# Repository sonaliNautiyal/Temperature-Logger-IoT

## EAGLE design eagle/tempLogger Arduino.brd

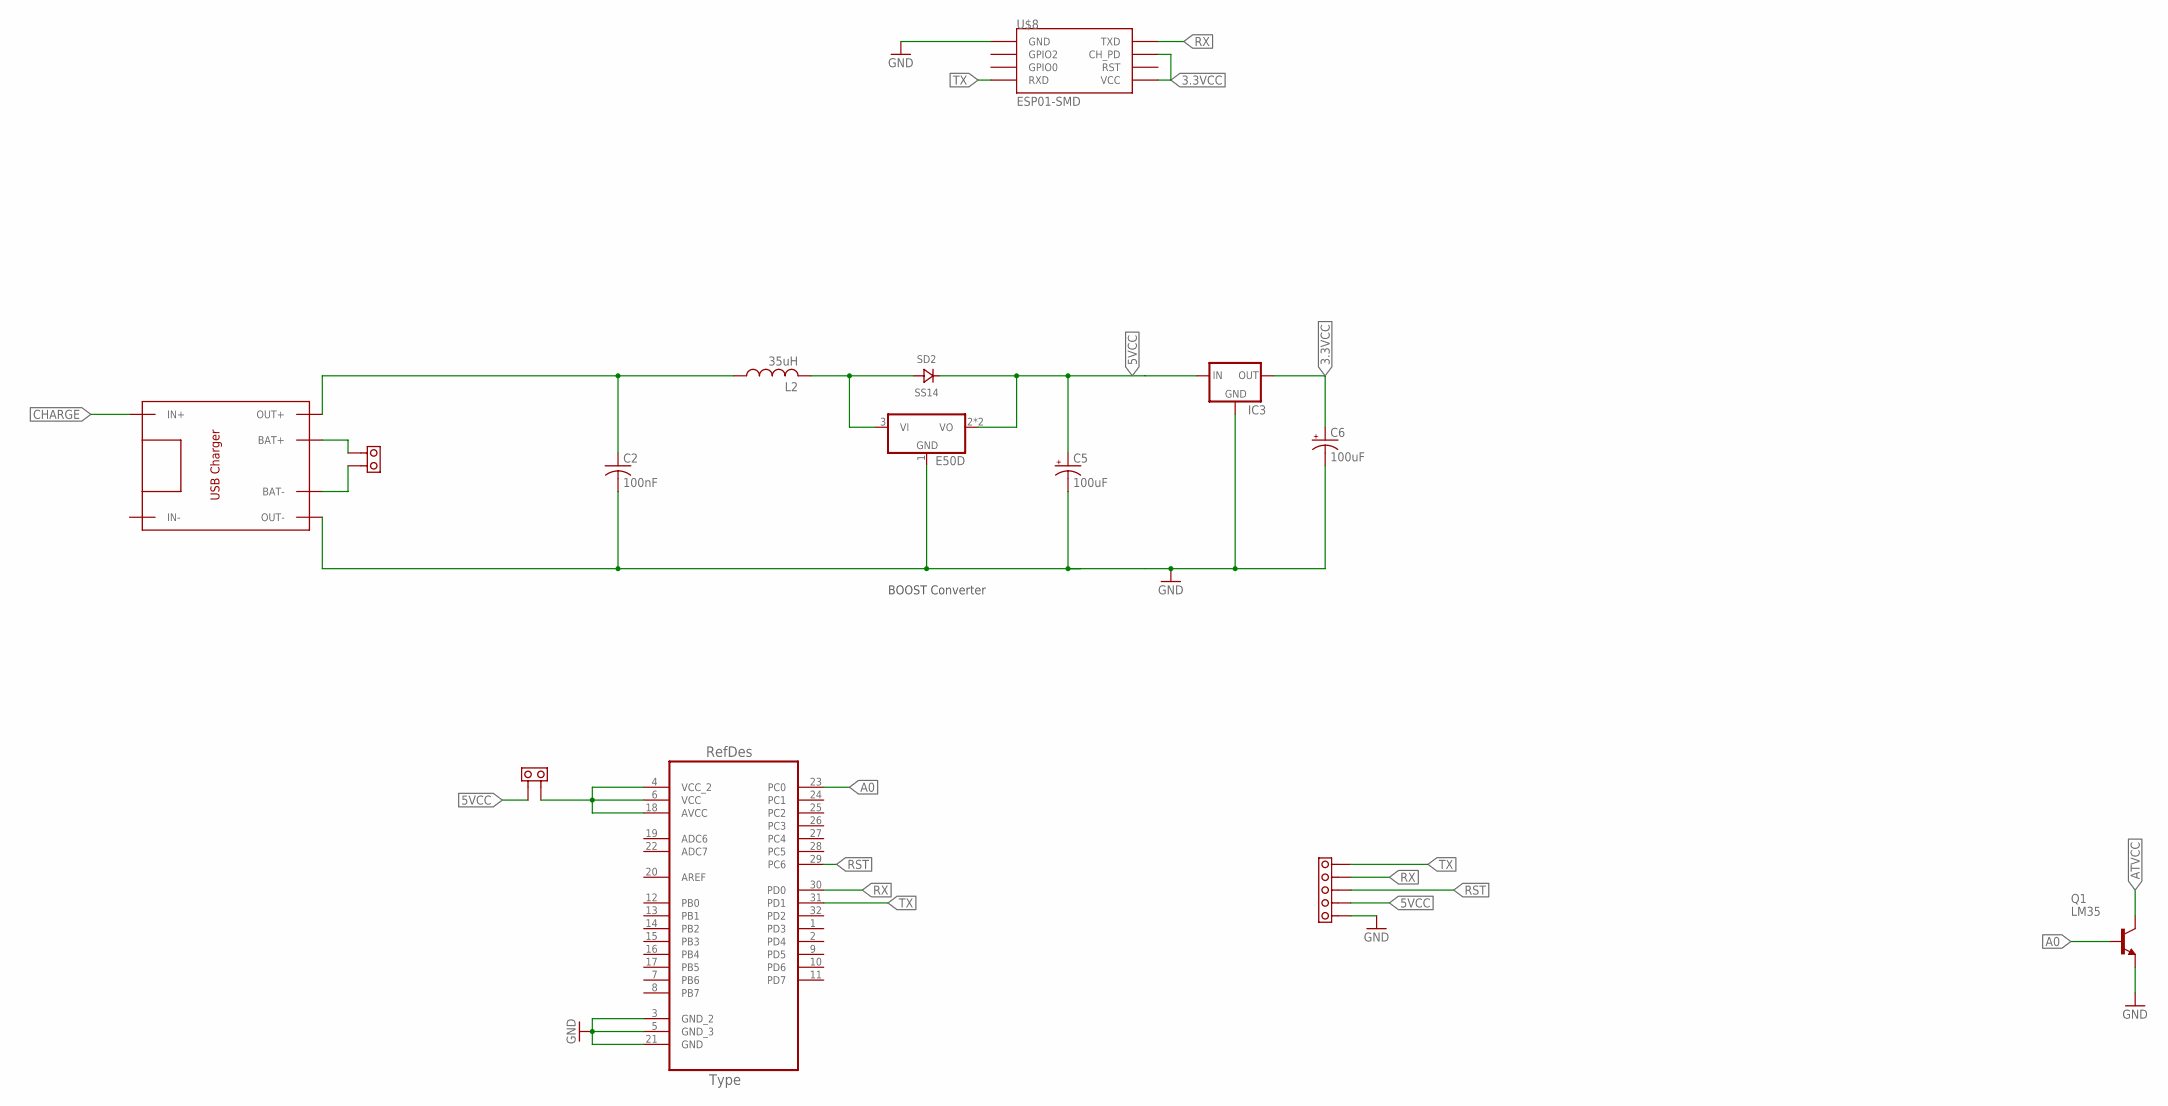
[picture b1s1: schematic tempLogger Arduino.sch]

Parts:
C2: 100nF; C1206
C5: 100uF; 150CLZ-0810
C6: 100uF; 153CLV-0405
IC2: E50D; SOT89
IC3: LM1117; SOT223
L2: 35uH; POWER-CHOKE_WE-TPC
Q1: LM35; TO92-EBC
SD2: SS14; DO214
U1: ATMEGA328P-AU; QFP80P900X900X120-32N
U$2: TP4056
U$3: BERG_5
U$4, U$5: BERG_2
U$8: ESP01-SMD; ESP01_SMD

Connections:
3.3VCC: C6.+, IC3.2 (OUT), U$8.CH_PD, U$8.VCC
5VCC: C5.+, IC2.2 (VO), IC2.2@1 (VO), IC3.3 (IN), SD2.CATHODE, U$3.H, U$5.F
A0: Q1.B, U1.23 (PC0)
ATVCC: Q1.C, U1.4 (VCC_2), U1.6 (VCC), U1.18 (AVCC), U$5.E
CHARGE: U$2.IN+
GND: C2.2, C5.-, C6.-, IC2.1 (GND), IC3.1 (GND), Q1.E, U1.3 (GND_2), U1.5 (GND_3), U1.21 (GND), U$2.OUT-, U$3.I, U$8.GND
unnamed: IC2.3 (VI), L2.2, SD2.ANODE
unnamed: U$2.BAT+, U$4.F
unnamed: U$2.BAT-, U$4.E
unnamed: C2.1, L2.1, U$2.OUT+
RST: U1.29 (PC6), U$3.G
RX: U1.30 (PD0), U$3.F, U$8.TX (TXD)
TX: U1.31 (PD1), U$3.E, U$8.RX (RXD)

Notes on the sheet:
BOOST Converter

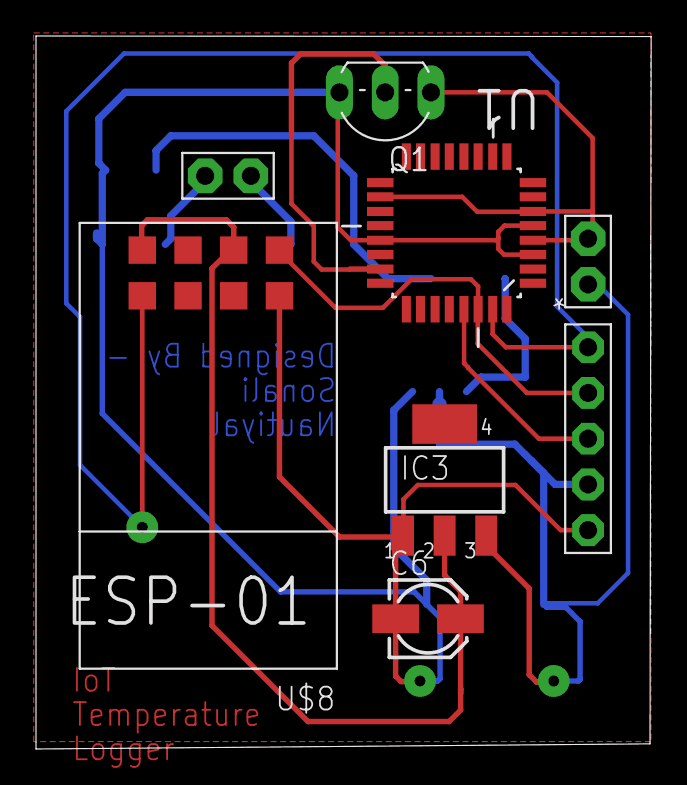
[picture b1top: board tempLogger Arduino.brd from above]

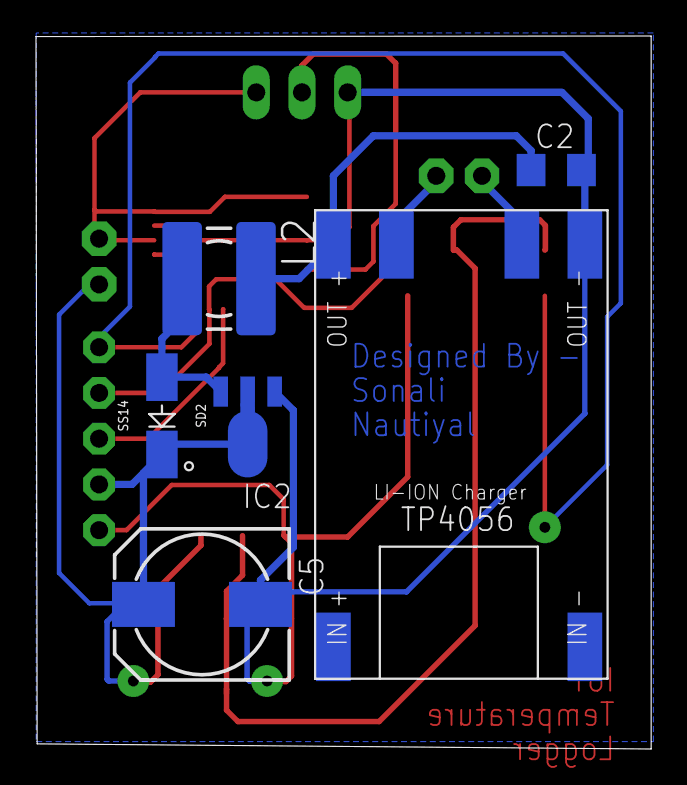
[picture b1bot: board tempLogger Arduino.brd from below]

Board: 2 copper layers, 34.2 x 39.6 mm, 14 parts (6 on the bottom side), 12 nets.

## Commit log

2017-10-02 ADD: Initial adding of all files
2017-11-05 ADD: Arduino Code UPDATE: Restructure the files
2017-11-05 UPDATE: Commented the code
2017-11-05 ADD: comment
2017-11-06 ADD: Documents
2017-11-06 Update: Eagle project file
2017-11-07 ADD: gitignore
2017-11-07 Add: Testing
